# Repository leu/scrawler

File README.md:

# The Scrawler
The name of this keyboard is the Scrawler.

It was inspired by this YouTube video: https://www.youtube.com/watch?v=thOifuHs6eY. It was born of wanting to experiment with a hexagonal tiling layout for keyboards. I currently have no plans to continue work on this project, as it is time consuming and many of the challenges are in the domain of material science and physical design, and I would rather spend my time in my personal specialisation of programming and computer science. But in case you have any questions, feel free to reach out to me at in.lieu.of.leu@gmail.com!

This repository contains all of my notes, PCB designs, and CAD files for 3D print for the Scrawler.

Second prototype:

First prototype:

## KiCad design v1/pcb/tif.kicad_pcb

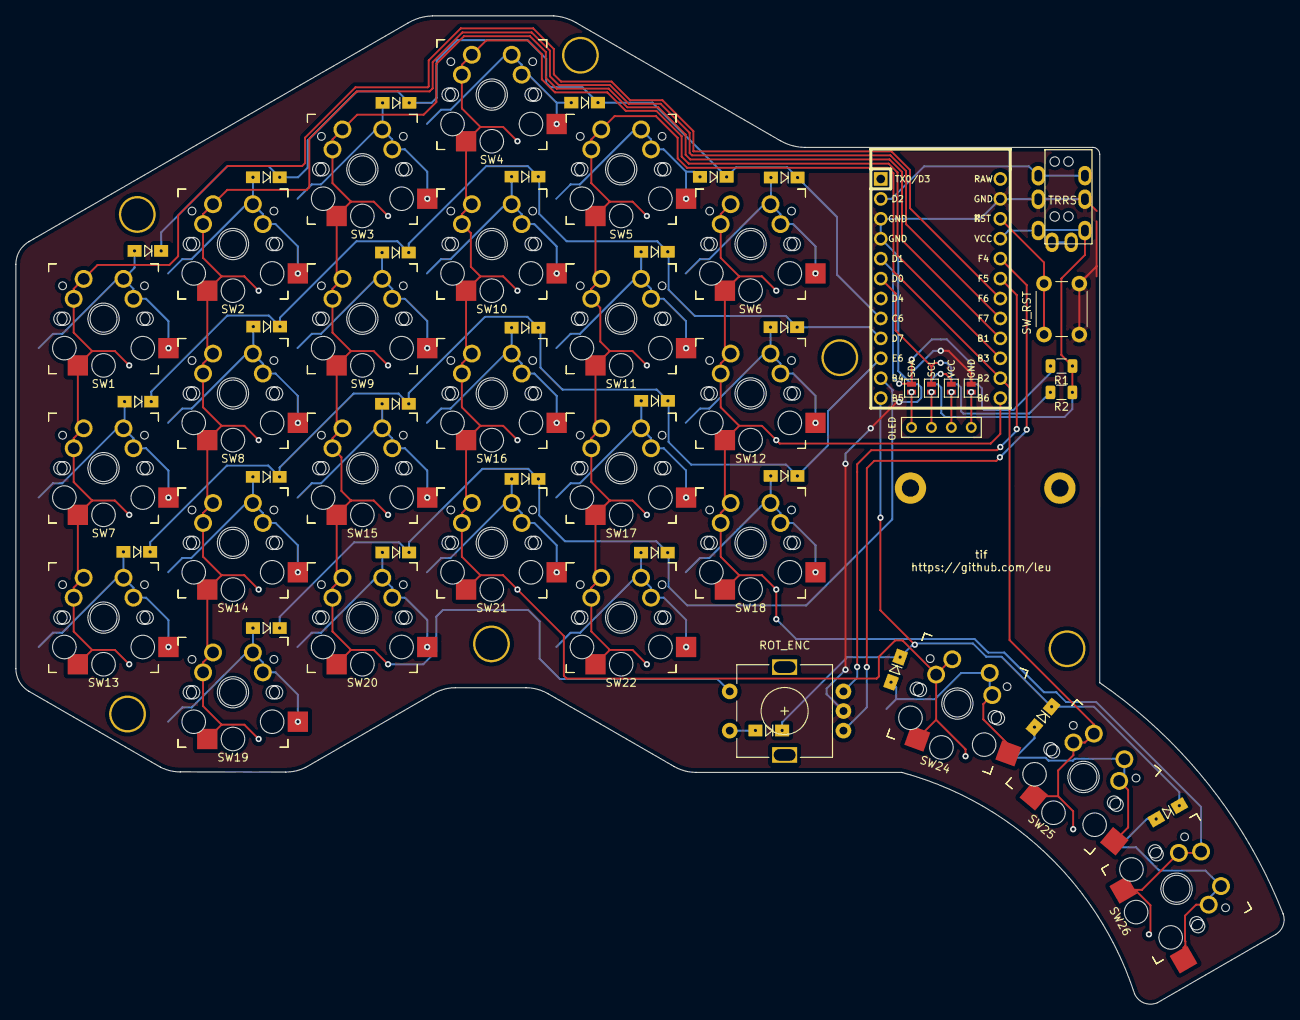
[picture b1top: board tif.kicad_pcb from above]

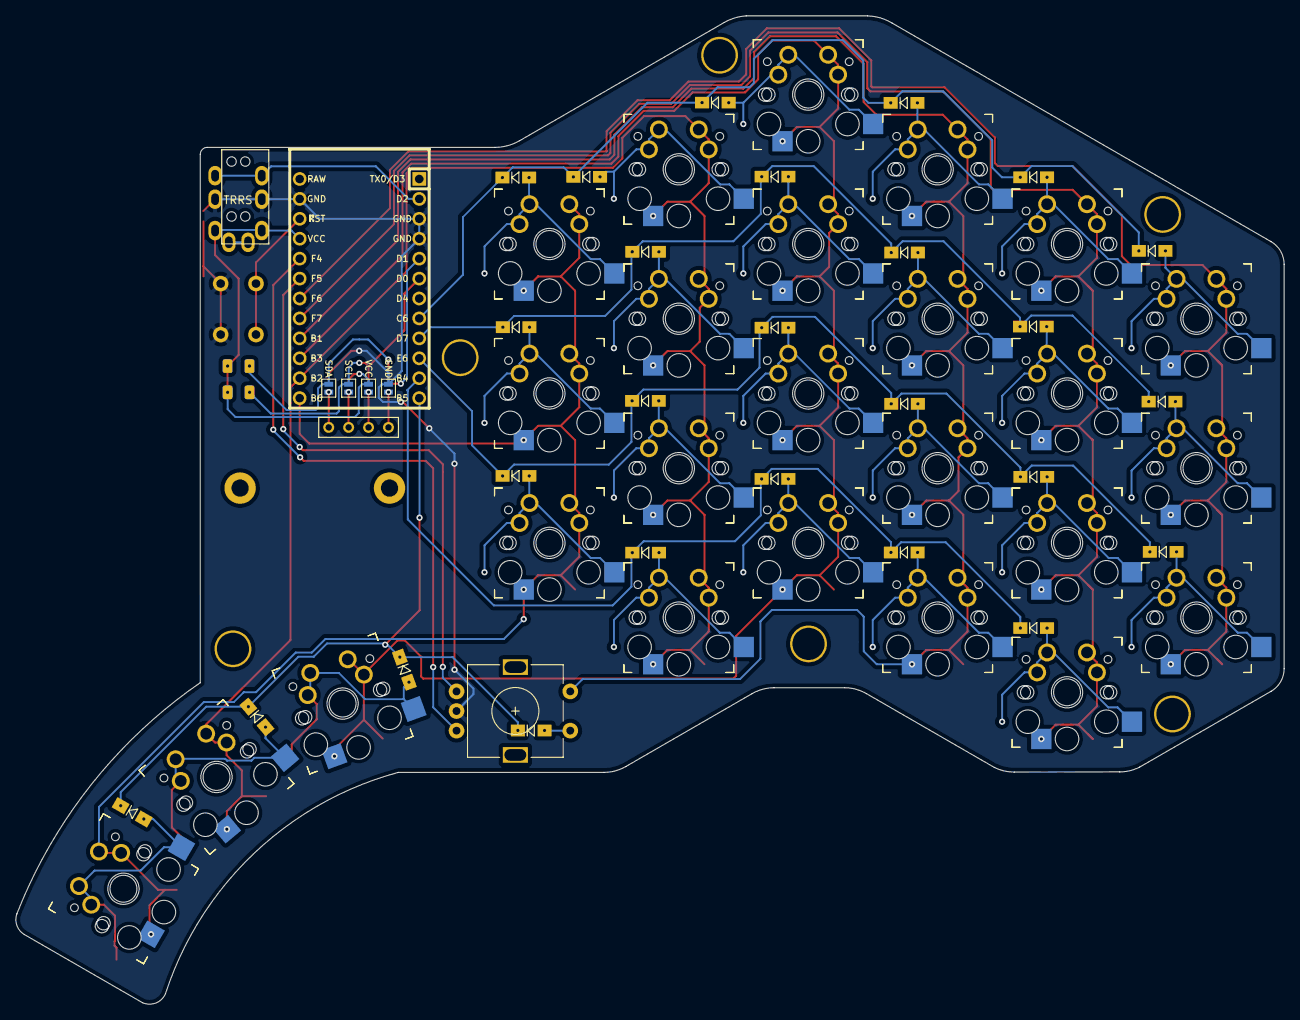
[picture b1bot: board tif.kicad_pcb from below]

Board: 2 copper layers, 161.7 x 126.0 mm, 99 parts (4 on the bottom side), 49 nets.

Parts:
D1, D2, D3, D4, D5, D6, D7, D8, D9, D10, D11, D12, D13, D14, D15, D16, D17, D18, D19, D20, D21, D22, D23, D24, D25, D26: D; Diode_SOD123
H1, H2, H3, H4, H5, H6: Hole; HOLE_M2_TH
H7, H8: Hole; M2_HOLE_PCB
J2: MJ-4PP-9
JP1, JP8: GND; Jumper
JP2, JP7: VCC; Jumper
JP3, JP6: SCL; Jumper
JP4, JP5: SDA; Jumper
OLED: OLED; OLED_4Pin
R1, R2: R; R_1206_DoubleSided
ROT_ENC: Rotary_Encoder_Switch; RotaryEncoder_Alps_EC11E-Switch_Vertical_H20mm-keebio_modif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
RSW1: SW_RST; SW_PUSH_6mm
SW1, SW2, SW3, SW4, SW5, SW6, SW7, SW8, SW9, SW10, SW11, SW12, SW13, SW14, SW15, SW16, SW17, SW18, SW19, SW20, SW21, SW22, SW24, SW25, SW26: SW_PUSH; MX_reversible
SW1B1, SW2B1, SW3B1, SW4B1, SW5B1, SW6B1, SW7B1, SW8B1, SW9B1, SW10B1, SW11B1, SW12B1, SW13B1, SW14B1, SW15B1, SW16B1, SW17B1, SW18B1, SW19B1, SW20B1, SW21B1, SW22B1, SW24B1, SW25B1, SW26B1: SW_PUSH; PG1350_socket_reversible
U1: ProMicro; ArduinoProMicro

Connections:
COL0: SW1.1, SW1B1.1, SW7.1, SW7B1.1, SW13.1, SW13B1.1, U1.18
COL1: SW2.1, SW2B1.1, SW8.1, SW8B1.1, SW14.1, SW14B1.1, SW19.1, SW19B1.1, U1.17
COL2: ROT_ENC.S1, SW3.1, SW3B1.1, SW9.1, SW9B1.1, SW15.1, SW15B1.1, SW20.1, SW20B1.1, U1.16
COL3: SW4.1, SW4B1.1, SW10.1, SW10B1.1, SW16.1, SW16B1.1, SW21.1, SW21B1.1, SW24.1, SW24B1.1, U1.15
COL4: SW5.1, SW5B1.1, SW11.1, SW11B1.1, SW17.1, SW17B1.1, SW22.1, SW22B1.1, SW25.1, SW25B1.1, U1.14
COL5: SW6.1, SW6B1.1, SW12.1, SW12B1.1, SW18.1, SW18B1.1, SW26.1, SW26B1.1, U1.13
DATA: J2.B, U1.2
ENCA: ROT_ENC.A, U1.20
ENCB: ROT_ENC.B, U1.19
GND: J2.C, JP1.2, JP8.2, ROT_ENC.C, RSW1.1, U1.3, U1.4, U1.23
unnamed: D1.2, SW1.2, SW1B1.2
unnamed: D2.2, SW2.2, SW2B1.2
unnamed: D3.2, SW3.2, SW3B1.2
unnamed: D4.2, SW4.2, SW4B1.2
unnamed: D5.2, SW5.2, SW5B1.2
unnamed: D6.2, SW6.2, SW6B1.2
unnamed: D7.2, SW7.2, SW7B1.2
unnamed: D8.2, SW8.2, SW8B1.2
unnamed: D9.2, SW9.2, SW9B1.2
unnamed: D10.2, SW10.2, SW10B1.2
unnamed: D11.2, SW11.2, SW11B1.2
unnamed: D12.2, SW12.2, SW12B1.2
unnamed: D13.2, SW13.2, SW13B1.2
unnamed: D14.2, SW14.2, SW14B1.2
unnamed: D15.2, SW15.2, SW15B1.2
unnamed: D16.2, SW16.2, SW16B1.2
unnamed: D17.2, SW17.2, SW17B1.2
unnamed: D18.2, SW18.2, SW18B1.2
unnamed: D19.2, SW19.2, SW19B1.2
unnamed: D20.2, SW20.2, SW20B1.2
unnamed: D21.2, SW21.2, SW21B1.2
unnamed: D22.2, SW22.2, SW22B1.2
unnamed: D24.2, SW24.2, SW24B1.2
unnamed: D25.2, SW25.2, SW25B1.2
unnamed: D26.2, SW26.2, SW26B1.2
unnamed: JP4.1, JP8.1, OLED.1
unnamed: JP3.1, JP7.1, OLED.2
unnamed: JP2.1, JP6.1, OLED.3
unnamed: JP1.1, JP5.1, OLED.4
RESET: RSW1.2, U1.22
ROW0: D1.1, D2.1, D3.1, D4.1, D5.1, D6.1, U1.8
ROW1: D7.1, D8.1, D9.1, D10.1, D11.1, D12.1, U1.9
ROW2: D13.1, D14.1, D15.1, D16.1, D17.1, D18.1, U1.10
ROW3: D19.1, D20.1, D21.1, D22.1, U1.11
ROW4: D23.1, D24.1, D25.1, D26.1, U1.12
SCL: JP3.2, JP6.2, R2.2, U1.6
SDA: JP4.2, JP5.2, R1.2, U1.5
SW23B: D23.2, ROT_ENC.S2
VCC: J2.D, JP2.2, JP7.2, R1.1, R2.1, U1.21

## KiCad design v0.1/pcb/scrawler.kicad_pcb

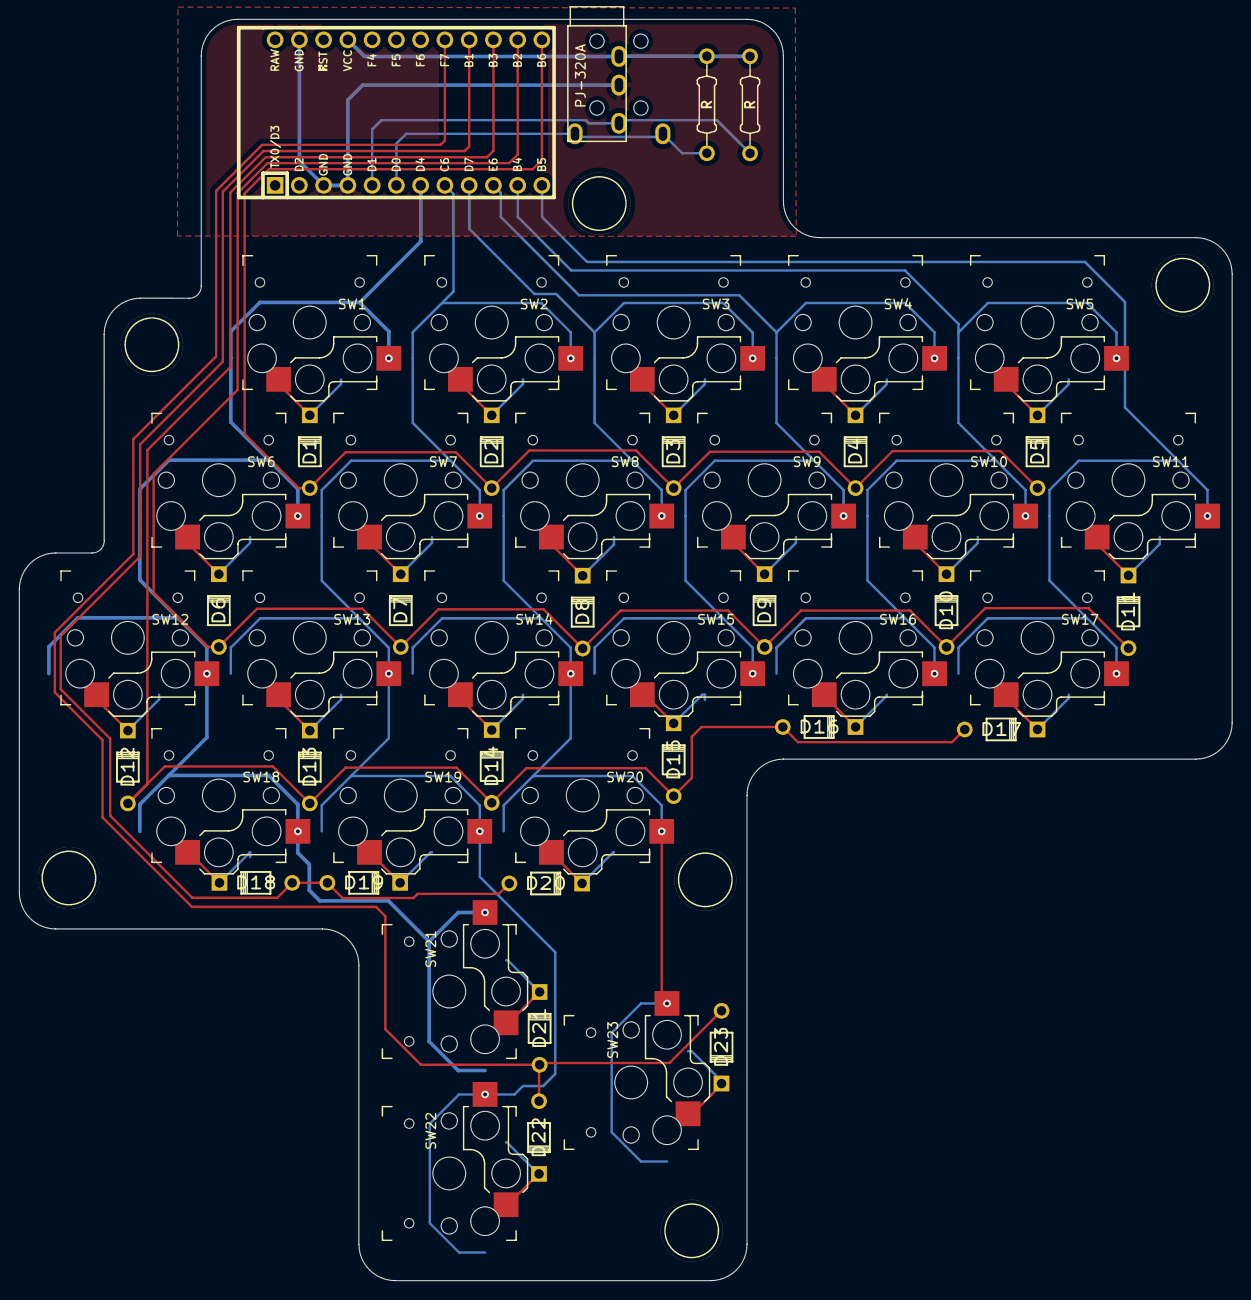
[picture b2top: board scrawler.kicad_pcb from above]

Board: 2 copper layers, 127.0 x 132.1 mm, 56 parts (0 on the bottom side), 38 nets.

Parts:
D1, D2, D3, D4, D5, D6, D7, D8, D9, D10, D11, D12, D13, D14, D15, D16, D17, D18, D19, D20, D21, D22, D23: diode; Diode
H1, H2, H3, H4, H5, H6: Hole; MountingHole
R1, R2: R; Resistor
SW1, SW2, SW3, SW4, SW5, SW6, SW7, SW8, SW9, SW10, SW11, SW12, SW13, SW14, SW15, SW16, SW17, SW18, SW19, SW20, SW21, SW22, SW23: switch; Kailh_socket_PG1350_reversible
U1: TRRS; TRRS-PJ-320A-dual
U2: ProMicro; ArduinoProMicro

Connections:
COL0: SW1.2, SW6.2, SW12.2, SW18.2, SW21.2, U2.7
COL1: SW2.2, SW7.2, SW13.2, SW19.2, SW22.2, U2.8
COL2: SW3.2, SW8.2, SW14.2, SW20.2, SW23.2, U2.9
COL3: SW4.2, SW9.2, SW15.2, U2.10
COL4: SW5.2, SW10.2, SW16.2, U2.11
COL5: SW11.2, SW17.2, U2.12
GND: U1.3, U2.3, U2.4, U2.23
unnamed: D1.2, SW1.1
unnamed: D2.2, SW2.1
unnamed: D3.2, SW3.1
unnamed: D4.2, SW4.1
unnamed: D5.2, SW5.1
unnamed: D6.2, SW6.1
unnamed: D7.2, SW7.1
unnamed: D8.2, SW8.1
unnamed: D9.2, SW9.1
unnamed: D10.2, SW10.1
unnamed: D11.2, SW11.1
unnamed: D12.2, SW12.1
unnamed: D13.2, SW13.1
unnamed: D14.2, SW14.1
unnamed: D15.2, SW15.1
unnamed: D16.2, SW16.1
unnamed: D17.2, SW17.1
unnamed: D18.2, SW18.1
unnamed: D19.2, SW19.1
unnamed: D20.2, SW20.1
unnamed: D21.2, SW21.1
unnamed: D22.2, SW22.1
unnamed: D23.2, SW23.1
ROW0: D1.1, D2.1, D3.1, D4.1, D5.1, U2.13
ROW1: D6.1, D7.1, D8.1, D9.1, D10.1, D11.1, U2.14
ROW2: D12.1, D13.1, D14.1, D15.1, D16.1, D17.1, U2.15
ROW3: D18.1, D19.1, D20.1, U2.16
ROW4: D21.1, D22.1, D23.1, U2.17
SCL: R2.2, U1.1, U2.6
SDA: R1.2, U1.2, U2.5
VCC: R1.1, R2.1, U1.4, U2.21

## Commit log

2021-05-10 files from desktop
2021-05-10 fix pcb
2021-05-10 fixed pcb
2021-05-10 submodules
2021-05-10 footprints
2021-05-10 stuff
2021-05-12 update design file
2021-05-12 started design, made components list
2021-05-12 laptop commit
2021-05-15 change name of jpg
2021-05-18 decided no resistors/switch for now
2021-05-19 started physical pcb
2021-05-20 finished routing
2021-05-20 gerbers
2021-05-26 put design files in folder
2021-05-28 clean root dir
2021-05-30 fix readme picture
2021-06-02 keycap
2021-06-02 made rectangle keycap and bottom plate template
2021-06-06 Update design
2021-06-07 Update keymap
2021-06-08 stl file
2021-06-08 case stl
2021-06-08 kicad dxf pdf
2021-06-08 inkscape case
2021-06-08 high res pdf
2021-06-08 freecad dxf
2021-06-08 new inkscape dxf
2021-06-08 clean
2021-06-09 stl files
2021-07-12 add prototype images
2021-07-12 showcase prototype
2021-07-13 update notes
2021-07-29 restructure for versions, clean design notes
2021-08-07 v1.0
2021-08-21 add submodules
2021-08-21 add keyswitches library
2021-08-21 pcb prfinished
2021-08-22 assigned footprints
2021-08-22 placed main switches in physical pcb
2021-08-26 pcb done
2021-08-27 pcb plate finished
2021-08-28 generated gerber files
2021-09-19 update keyboard name from scrawler to tif
2021-09-20 notes
2021-09-20 pcb plate
2021-09-20 renamed to tif
2021-09-20 keycap stem work
2021-09-24 started on top plate
2021-09-24 hole for rotary encoder
2021-09-24 finished top plate switch mounts, switched holes on plate
2021-09-24 top plate outline done
2021-09-24 top plate finished
2021-09-24 bottom plate finished
2024-04-25 Update README.md, update keyboard's name from tif to Scrawler
2025-09-22 Include image of second prototype
